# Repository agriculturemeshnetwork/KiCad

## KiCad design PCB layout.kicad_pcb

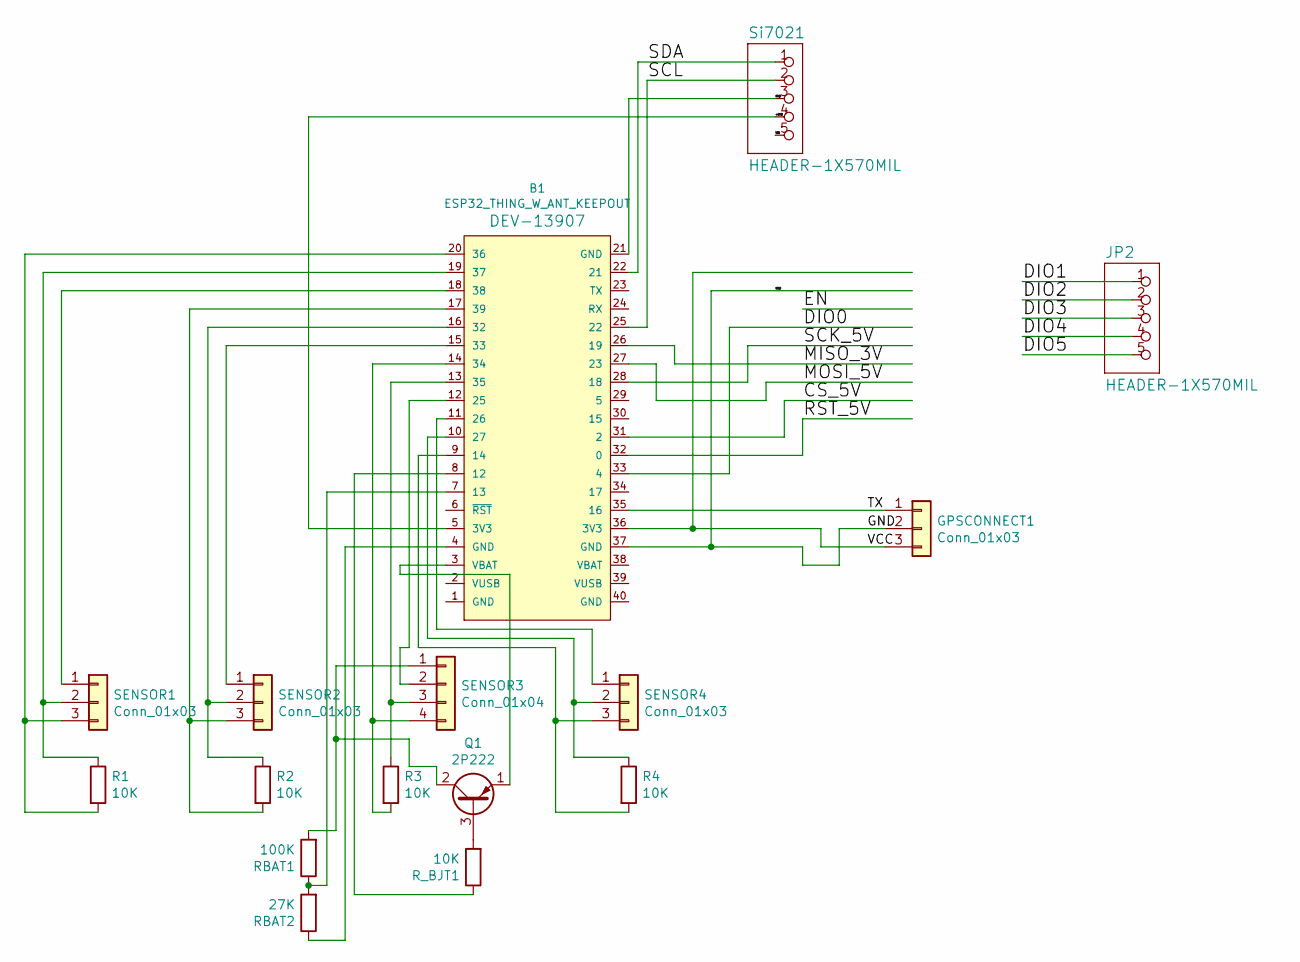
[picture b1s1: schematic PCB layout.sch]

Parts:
B1: ESP32_THING_W_ANT_KEEPOUT; ESP32_THING_NO_ANT
GPSCONNECT1: Conn_01x03; JST_PH_S3B-PH-K_1x03_P2.00mm_Horizontal
JP2: HEADER-1X570MIL; 1X05_ROUND_70
Q1: 2P222; TO-92L_Inline_Wide
R1, R2, R3, R4: 10K; 0805-NO
RBAT1: 100K; 0805-NO
RBAT2: 27K; 0805-NO
R_BJT1: 10K; 0805-NO
SENSOR1, SENSOR2, SENSOR4: Conn_01x03; TerminalBlock_Altech_AK300-3_P5.00mm
SENSOR3: Conn_01x04; TerminalBlock_Altech_AK300-4_P5.00mm
Si7021: HEADER-1X570MIL; Altech_AK300_1x05_P5.00mm_45-Degree

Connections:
/+3V3: B1.5 (3V3), Si7021.4
/CS_5V: B1.31 (2); also elsewhere on the board
/DIO0: B1.33 (4); also elsewhere on the board
/DIO1: JP2.1
/DIO2: JP2.2
/DIO3: JP2.3
/DIO4: JP2.4
/DIO5: JP2.5
/GND: B1.21 (GND), B1.37 (GND), GPSCONNECT1.2, Si7021.3
/MISO_3V: B1.26 (19); also elsewhere on the board
/MOSI_5V: B1.27 (23); also elsewhere on the board
/RST_5V: B1.32 (0); also elsewhere on the board
/SCK_5V: B1.28 (18); also elsewhere on the board
/SCL: B1.25 (22), Si7021.2
/SDA: B1.22 (21), Si7021.1
/TX: B1.35 (16), GPSCONNECT1.1
/VCC: B1.36 (3V3), GPSCONNECT1.3
/VIN: Si7021.5
unnamed: B1.3 (VBAT), Q1.1 (E)
unnamed: B1.4 (GND), RBAT2.1
unnamed: B1.7 (13), RBAT1.1, RBAT2.2
unnamed: B1.8 (12), R_BJT1.1
unnamed: B1.9 (14), R4.2, SENSOR4.3
unnamed: B1.10 (27), R4.1, SENSOR4.2
unnamed: B1.11 (26), SENSOR4.1
unnamed: B1.12 (25), SENSOR3.2
unnamed: B1.13 (35), R3.1, SENSOR3.3
unnamed: B1.14 (34), R3.2, SENSOR3.4
unnamed: B1.15 (33), SENSOR2.1
unnamed: B1.16 (32), R2.1, SENSOR2.2
unnamed: B1.17 (39), R2.2, SENSOR2.3
unnamed: B1.18 (38), SENSOR1.1
unnamed: B1.19 (37), R1.1, SENSOR1.2
unnamed: B1.20 (36), R1.2, SENSOR1.3
unnamed: Q1.2 (C), RBAT1.2, SENSOR3.1
unnamed: Q1.3 (B), R_BJT1.2

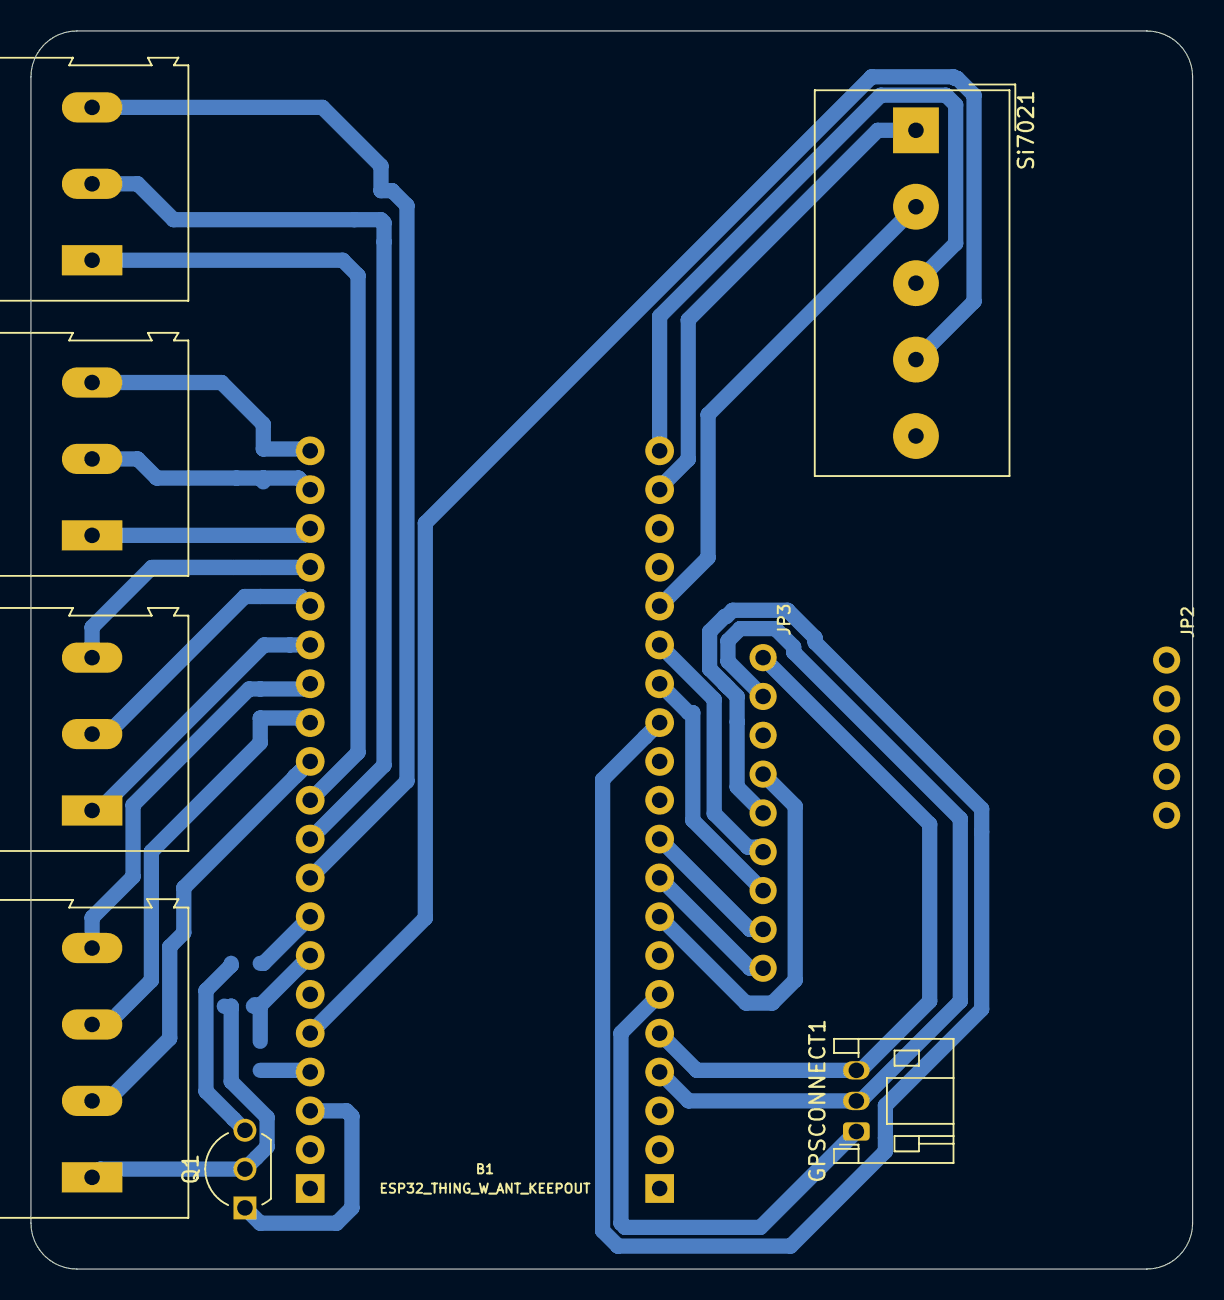
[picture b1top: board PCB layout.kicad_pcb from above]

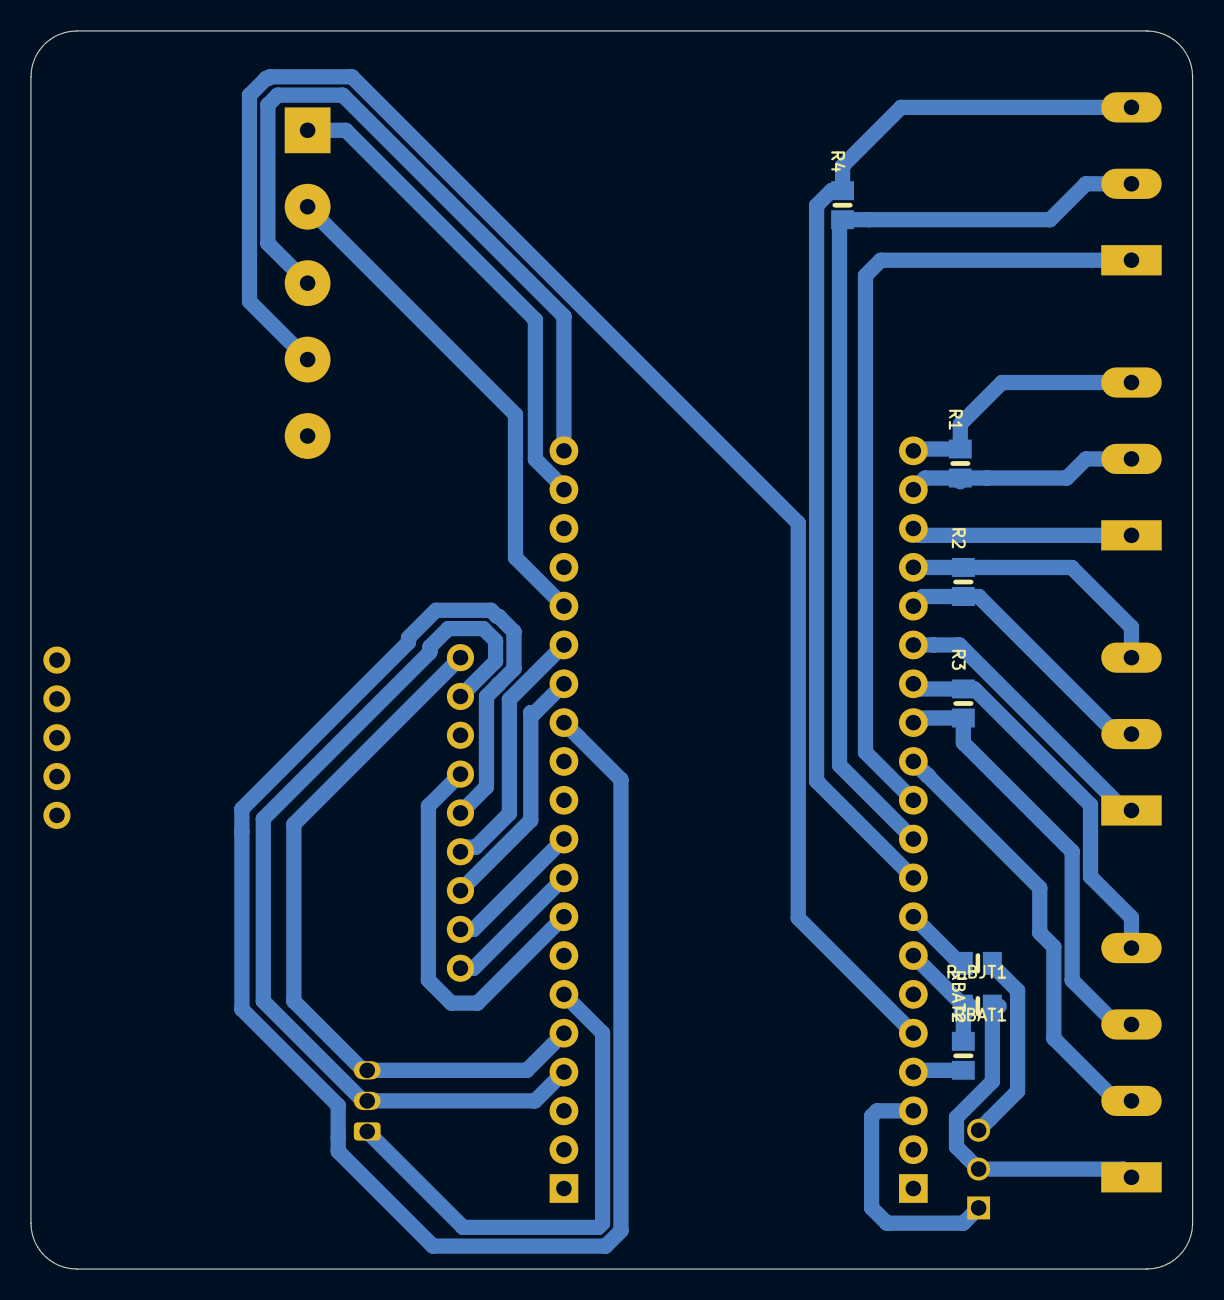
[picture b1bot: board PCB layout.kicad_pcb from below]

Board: 2 copper layers, 76.0 x 81.0 mm, 17 parts (7 on the bottom side), 30 nets.

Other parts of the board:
JP3: HEADER-1X970MIL; 1X09_ROUND_70

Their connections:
/CS_5V: JP3.8; also elsewhere on the board
/DIO0: JP3.4; also elsewhere on the board
/MISO_3V: JP3.6; also elsewhere on the board
/MOSI_5V: JP3.7; also elsewhere on the board
/RST_5V: JP3.9; also elsewhere on the board
/SCK_5V: JP3.5; also elsewhere on the board

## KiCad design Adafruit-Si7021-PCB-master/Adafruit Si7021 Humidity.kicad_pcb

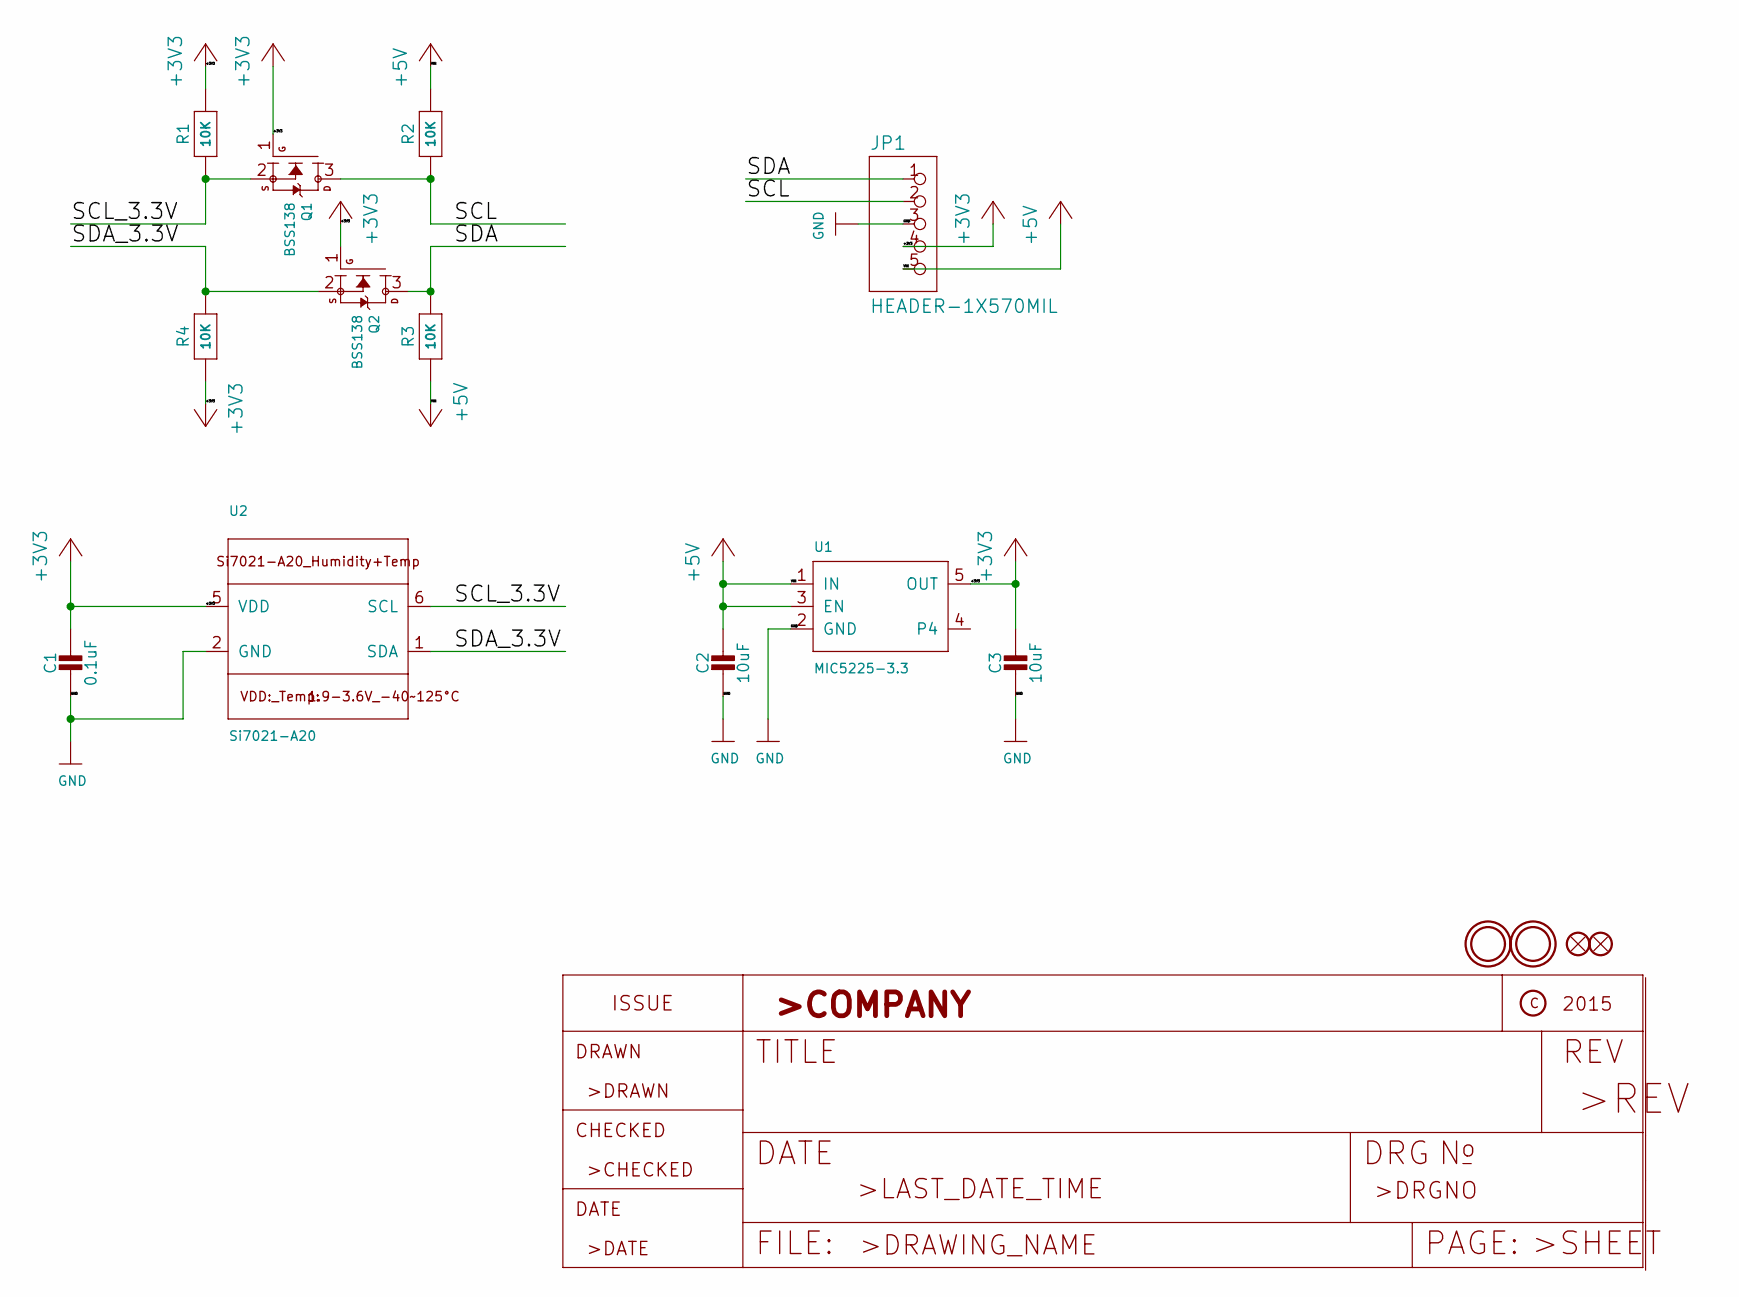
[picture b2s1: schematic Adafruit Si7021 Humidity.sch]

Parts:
C1: 0.1uF; 0805-NO
C2, C3: 10uF; 0805-NO
FID1, FID2: FIDUCIAL\"\"; FIDUCIAL_1MM
JP1: HEADER-1X570MIL; 1X05_ROUND_70
Q1, Q2: BSS138; SOT23-WIDE
R1, R2, R3, R4: 10K; 0805-NO
U1: MIC5225-3.3; SOT23-5
U2: Si7021-A20; DFN6_3X3_SI
U$6, U$7: MOUNTINGHOLE2.5; MOUNTINGHOLE_2.5_PLATED

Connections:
+3V3: C1.1, C3.1, JP1.4, Q1.1 (G), Q2.1 (G), R1.2, R4.1, U1.5 (OUT), U2.5 (VDD)
+5V: C2.1, JP1.5, R2.2, R3.1, U1.1 (IN), U1.3 (EN)
/SCL: JP1.2, Q1.3 (D), R2.1
/SCL_3.3V: Q1.2 (S), R1.1, U2.6 (SCL)
/SDA: JP1.1, Q2.3 (D), R3.2
/SDA_3.3V: Q2.2 (S), R4.2, U2.1 (SDA)
GND: C1.2, C2.2, C3.2, JP1.3, U1.2 (GND), U2.2 (GND)

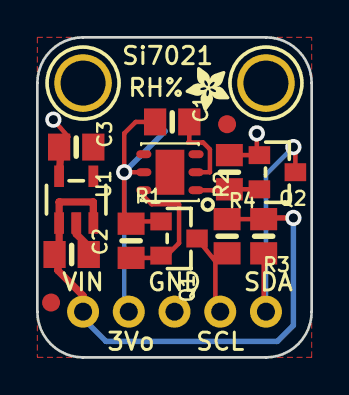
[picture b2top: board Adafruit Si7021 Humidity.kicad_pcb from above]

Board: 2 copper layers, 15.2 x 17.8 mm, 19 parts (0 on the bottom side), 7 nets.

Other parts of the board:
U$1: ADAFRUIT_2.5MM
U$9: PCBFEAT-REV-040
U$10: ADAFRUIT_3.5MM

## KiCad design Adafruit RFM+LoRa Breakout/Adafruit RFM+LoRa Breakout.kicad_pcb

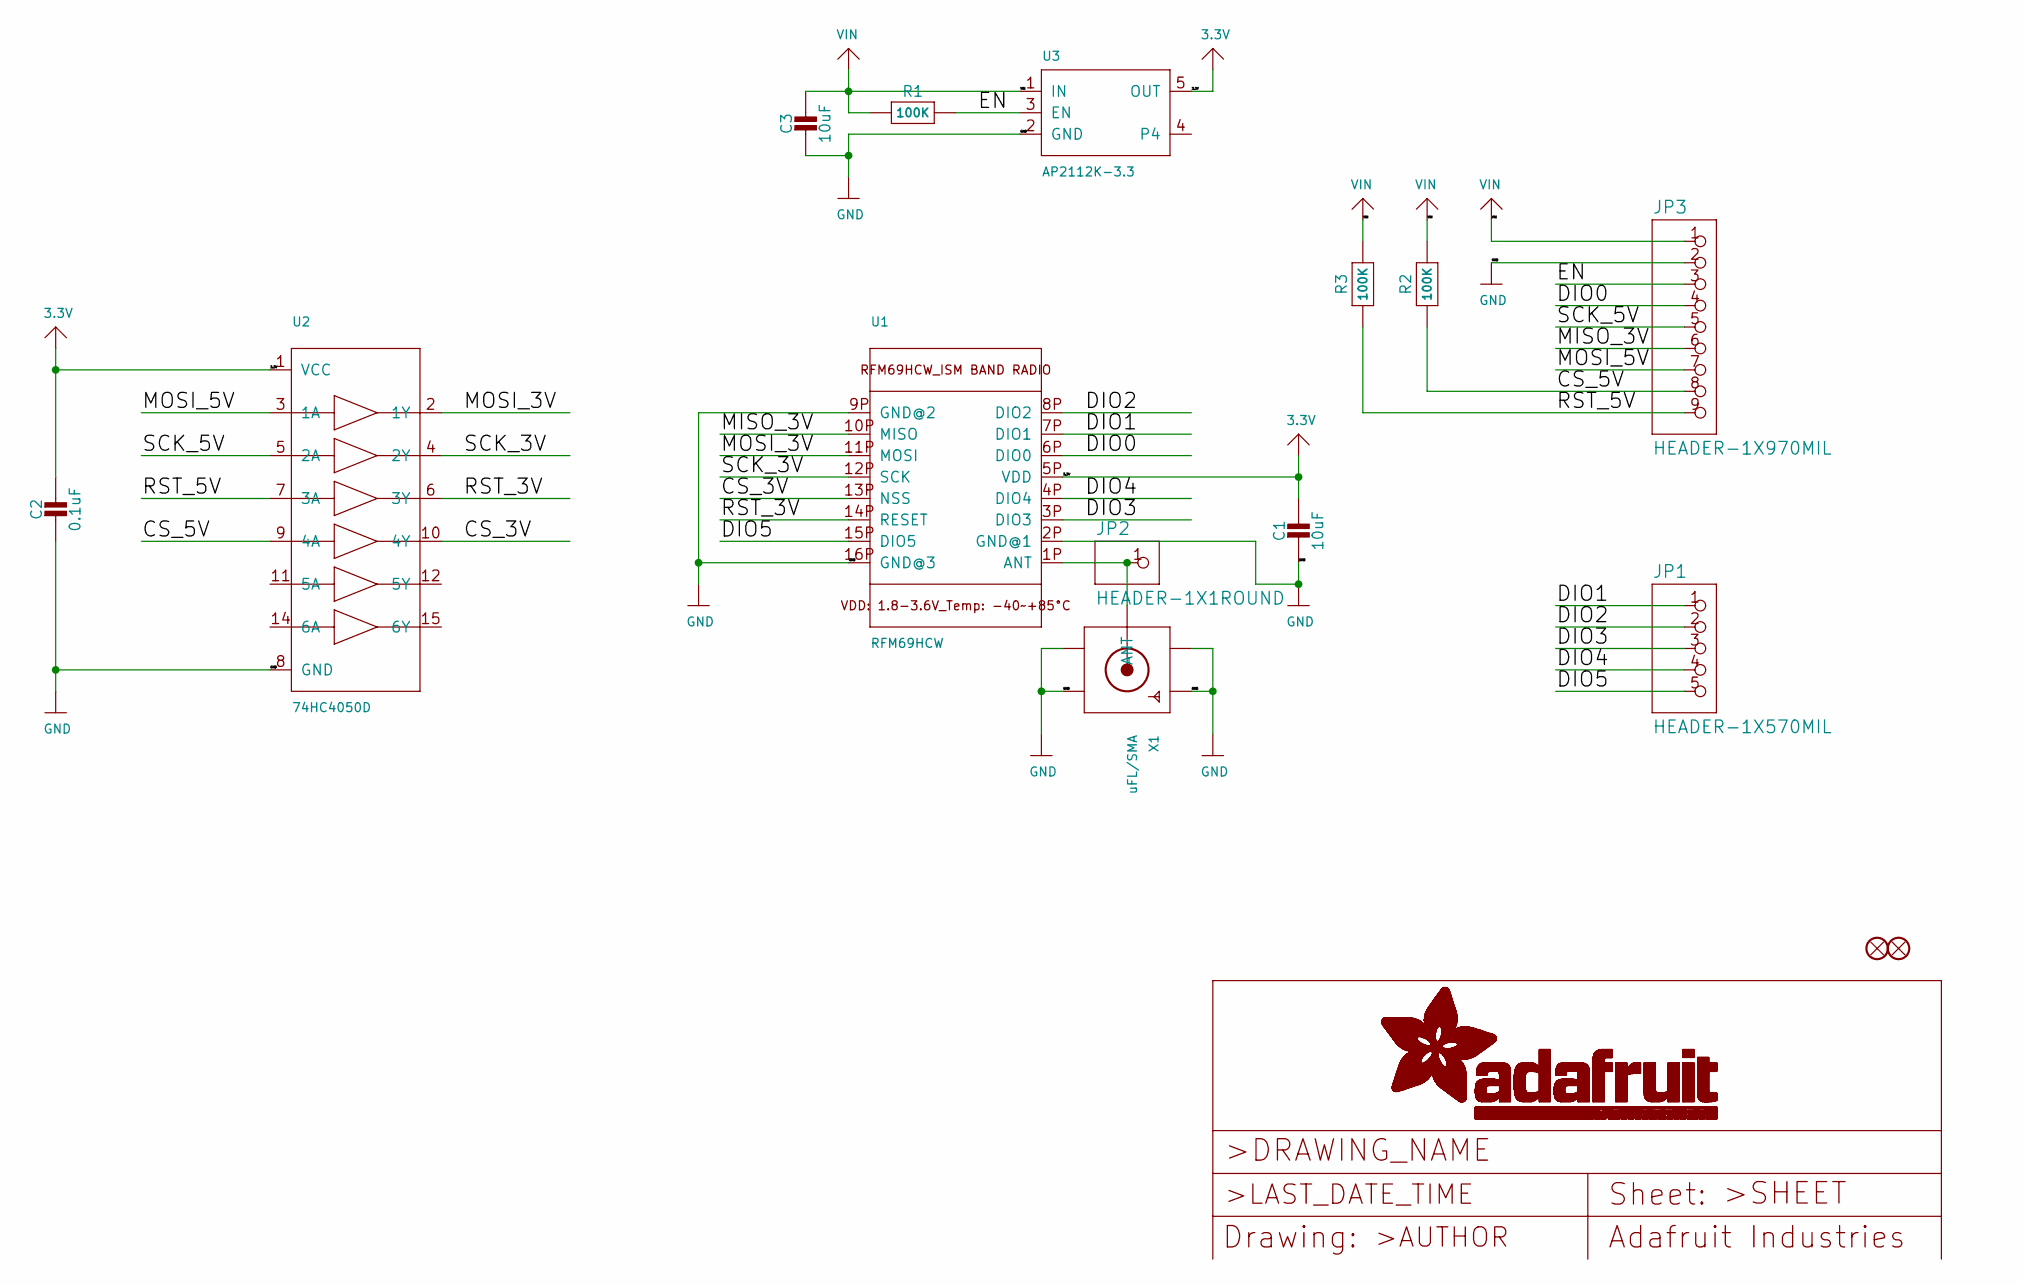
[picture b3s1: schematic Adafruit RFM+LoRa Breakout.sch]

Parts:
C1, C3: 10uF; 0805-NO
C2: 0.1uF; 0805-NO
FID1, FID2: FIDUCIAL\"\"; FIDUCIAL_1MM
JP1: HEADER-1X570MIL; 1X05_ROUND_70
JP2: HEADER-1X1ROUND; 1X01_ROUND
JP3: HEADER-1X970MIL; 1X09_ROUND_70
R1, R2, R3: 100K; 0805-NO
U1: RFM69HCW; RFMHCW_SMT
U2: 74HC4050D; TSSOP16
U3: AP2112K-3.3; SOT23-5
X1: uFL/SMA; SMA_EDGELAUNCH_UFL

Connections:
3.3V: C1.1, C2.1, U1.5P (VDD), U2.1 (VCC), U3.5 (OUT)
/CS_3V: U1.13P (NSS), U2.10 (4Y)
/CS_5V: JP3.8, R2.1, U2.9 (4A)
/DIO0: JP3.4, U1.6P (DIO0)
/DIO1: JP1.1, U1.7P (DIO1)
/DIO2: JP1.2, U1.8P (DIO2)
/DIO3: JP1.3, U1.3P (DIO3)
/DIO4: JP1.4, U1.4P (DIO4)
/DIO5: JP1.5, U1.15P (DIO5)
/EN: JP3.3, R1.2, U3.3 (EN)
/MISO_3V: JP3.6, U1.10P (MISO)
/MOSI_3V: U1.11P (MOSI), U2.2 (1Y)
/MOSI_5V: JP3.7, U2.3 (1A)
/RST_3V: U1.14P (RESET), U2.6 (3Y)
/RST_5V: JP3.9, R3.1, U2.7 (3A)
/SCK_3V: U1.12P (SCK), U2.4 (2Y)
/SCK_5V: JP3.5, U2.5 (2A)
GND: C1.2, C2.2, C3.2, JP3.2, U1.2P (GND@1), U1.9P (GND@2), U1.16P (GND@3), U2.8 (GND), U3.2 (GND), X1.GND@1 (GND1), X1.GND@2 (GND2), X1.GND@3 (GND3), X1.GND@4 (GND4)
unnamed: JP2.1, U1.1P (ANT), X1.P (ANT)
VIN: C3.1, JP3.1, R1.1, R2.2, R3.2, U3.1 (IN)

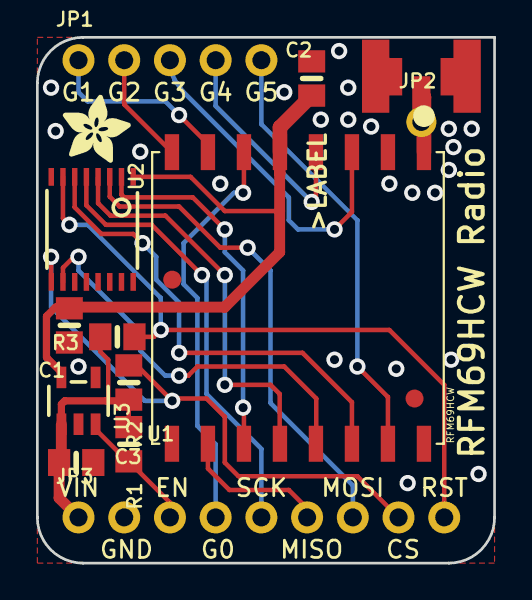
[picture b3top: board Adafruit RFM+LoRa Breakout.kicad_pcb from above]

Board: 2 copper layers, 25.4 x 29.2 mm, 18 parts (0 on the bottom side), 20 nets.

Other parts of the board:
U$8: ADAFRUIT_3.5MM
U$14: PCBFEAT-REV-040
U$19: ADAFRUIT_TEXT_20MM

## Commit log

2019-04-09 Version 1.1
